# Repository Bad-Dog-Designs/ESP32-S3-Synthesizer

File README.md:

Project overview:
A custom polyphonic synthesizer built around an ESP32-S3 audio engine communicating with multiple ATmega328p control boards via CAN bus at 500kbps. All boards share synth_params.h as the single source of truth for CAN message definitions.
Hardware boards:

ESP32-S3 — audio engine, MIDI input, I2S DAC output, CAN master
Oscillator boards (ATmega328p, up to 4) — dual oscillator control per board, board ID set by hardware jumpers (both open = board 0)
Commons board (ATmega328p) — filter, envelope, LFO, ring mod, play mode controls
Routing board (ATmega328p) — modulation matrix UI, 12 routes, LED matrix display
Patch board (ATmega328p, pending) — SD card patch storage UI, keypad, VFD/starburst display

ESP32-S3 pin assignments:

I2S: GPIO 4(BCK), 5(WS), 6(DOUT)
CAN TX/RX: GPIO 7/8
MIDI RX: GPIO 16
SD card: GPIO 9(CD), 10(CS), 11(MOSI), 12(SCK), 13(MISO)

Current file set (V11.0):

synth_v11.ino — setup(), loop(), task spawn only
synth_engine.h — all type/struct definitions, extern globals, function prototypes
synth_engine.cpp — globals, voice management, oscillator, filter, LFO, FM, audio task
synth_midi.h/.cpp — MIDI byte processing, noteOn/Off, voice allocation
synth_can.h/.cpp — TWAI setup, systemStartup, processCanMessages, sendCanAck
synth_params.h — shared CAN parameter definitions, all boards

Architecture:

Audio runs on Core 1 via audioTask(), CAN+MIDI runs on Core 0 via loop()
portMUX_TYPE voiceMux protects voice array cross-core access
NUM_VOICES_ACTIVE set dynamically from detected oscillator boards at startup (2 per board)
TWAI rx_queue_len=64 to handle full parameter dumps

Voice model:

Up to 8 voices (MAX_VOICES), typically 6 active (3 oscillator boards)
Even voices (0,2,4,6) are FM/sync masters per board pair
Odd voices (1,3,5,7) are FM/sync slaves — can sync to or be FM-modulated by their partner
FM: OSC_A (even) modulates OSC_B (odd) phase. fmEnabled, fmDepth on even voice. fmRatio on odd voice
Hard sync: per-board-pair, not global. syncEnabled only valid on odd voices
Solo: toggle per voice, restricts noteOn to soloed voices only
Clone: copies all timbre params including fmEnabled, fmDepth, fmRatio to all other voices. cloneActive global drives all clone LEDs on all boards simultaneously. Second press clears LEDs, cloned params remain

Signal chain per voice:
S+H → phaseInc | FM phase offset | Oscillator → Wavefold → SVF Filter → × envLevel × level × velocity
Waveforms: SAW, SINE, TRI, PULSE, CHAOS (logistic map), NOISE
Modifiers:

FOLD: post-oscillator waveshaper. foldEnabled, foldAmount (0-1), foldBias (-1 to +1)
S+H: independent pitch randomiser clock. shEnabled, shRate (0.5-40Hz), shRange (1-48 semitones)
FM: fmEnabled, fmDepth (0-1), fmRatio (0.5-8.0)

Play modes: POLY, DUO (half voices per note), UNISON (all voices per note)
Gain scaling by mode: UNISON=1.8f, DUO=2.0f, POLY=4.0f (tuned by ear)
SVF Filter: Low/Band/High pass. cutoffHz, resonance, envAmount (envelope→cutoff), keyTracking. Coefficients updated on each filter parameter change and at noteOn.
Envelope: ADSR. Times stored as float seconds. Coefficients (attackCoeff etc.) computed by updateEnvelopeRates() — must be called at startup and on any time change.
LFOs: 2× LFOs. 4 waveforms (SINE/TRI/CHAOS/S&H). Rate, delay, retrigger. No depth — depth is per-route. RETRIGGER is toggle: each CAN message flips state.
Ring modulator: 4 voice pair options. level, modMute.
Modulation routing (V11 — implementation pending):

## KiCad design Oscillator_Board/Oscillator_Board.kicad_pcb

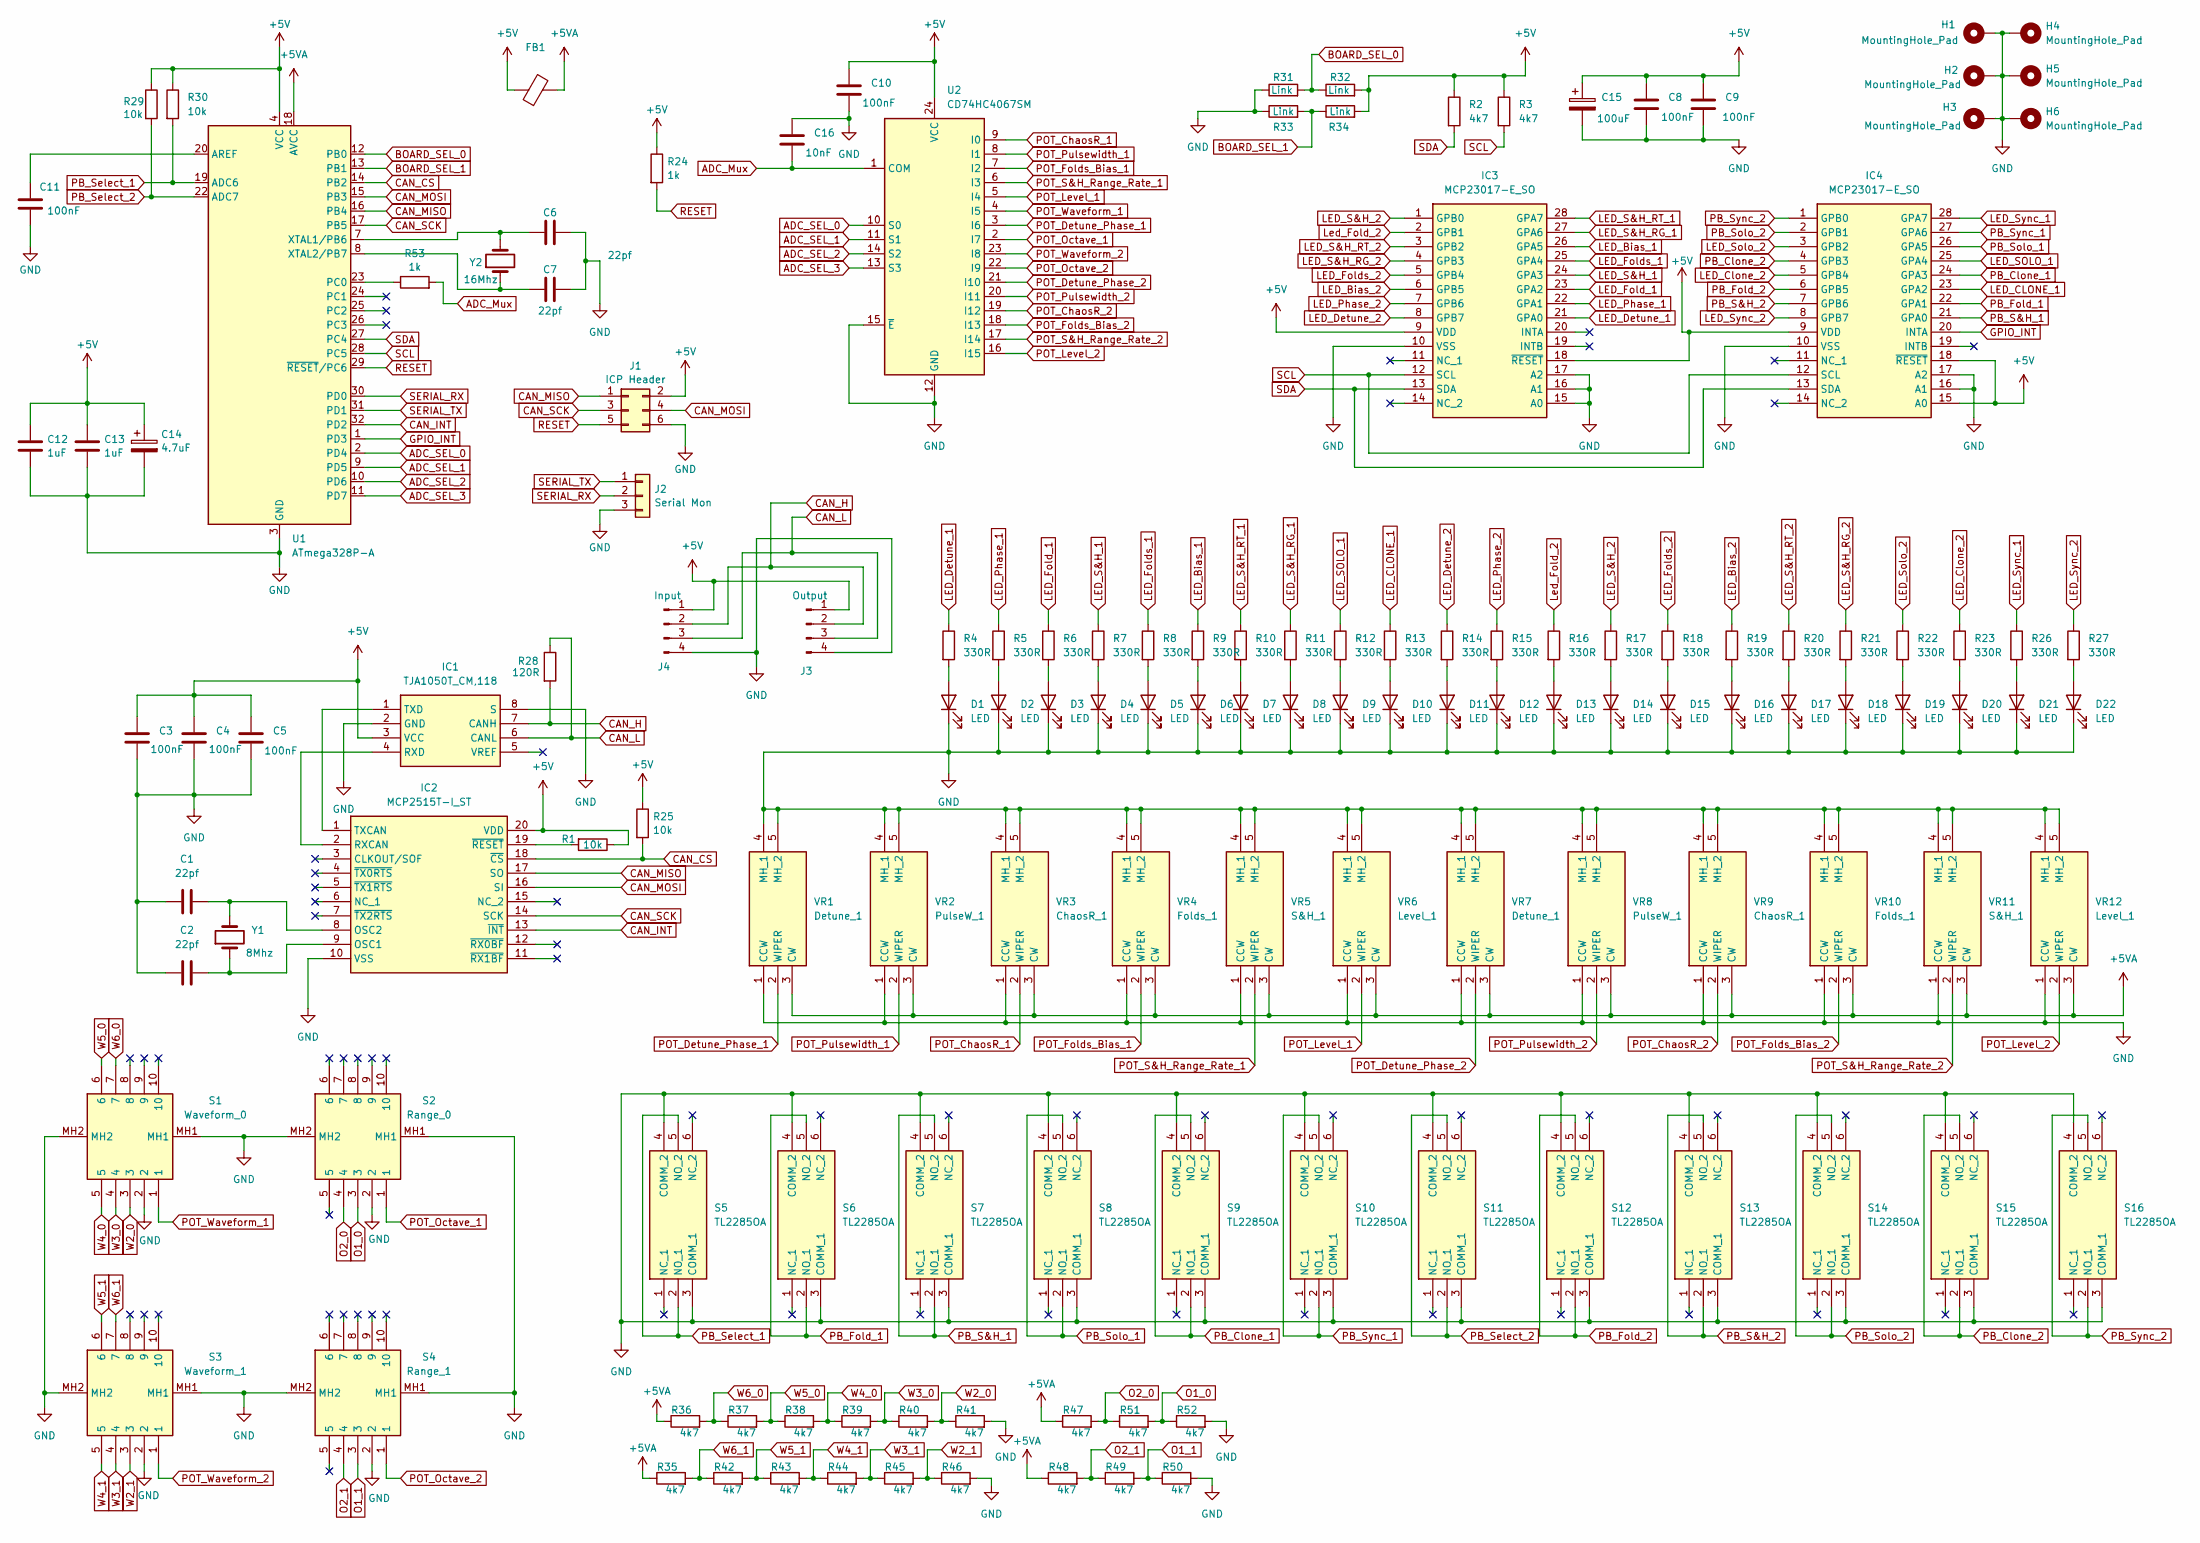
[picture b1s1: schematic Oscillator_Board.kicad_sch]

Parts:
C1, C2, C6, C7: 22pf; C_0805_2012Metric_Pad1.18x1.45mm_HandSolder
C3, C4, C5, C8, C9, C10, C11: 100nF; C_0805_2012Metric_Pad1.18x1.45mm_HandSolder
C12, C13: 1uF; C_0805_2012Metric_Pad1.18x1.45mm_HandSolder
C14: 4.7uF; CP_Radial_D4.0mm_P2.00mm
C15: 100uF; CP_Radial_D4.0mm_P2.00mm
C16: 10nF; C_0805_2012Metric_Pad1.18x1.45mm_HandSolder
D1, D2, D3, D4, D5, D6, D7, D8, D9, D10, D11, D12, D13, D14, D15, D16, D17, D18, D19, D20, D21, D22: LED; LED_D3.0mm_FlatTop
FB1: 10R; R_0805_2012Metric_Pad1.20x1.40mm_HandSolder
H1, H2, H3, H4, H5, H6: MountingHole_Pad; MountingHole_3.2mm_M3_DIN965_Pad
IC1: TJA1050T_CM,118; SOIC127P600X175-8N; Mouser Part Number 771-TJA1050T/CM118
IC2: MCP2515T-I_ST; SOP65P640X120-20N; Mouser Part Number 579-MCP2515T-I/ST
IC3, IC4: MCP23017-E_SO; SOIC127P1030X265-28N; Mouser Part Number 579-MCP23017-E/SO
J1: ICP Header; PinSocket_2x03_P2.54mm_Vertical
J2: Serial Mon; PinSocket_1x03_P2.54mm_Vertical
J3: Output; JST_EH_S4B-EH_1x04_P2.50mm_Horizontal
J4: Input; JST_EH_S4B-EH_1x04_P2.50mm_Horizontal
R1, R25, R29, R30: 10k; R_0603_1608Metric_Pad0.98x0.95mm_HandSolder
R2, R3, R35, R36, R37, R38, R39, R40, R41, R42, R43, R44, R45, R46, R47, R48, R49, R50, R51, R52: 4k7; R_0603_1608Metric_Pad0.98x0.95mm_HandSolder
R4, R5, R6, R7, R8, R9, R10, R11, R12, R13, R14, R15, R16, R17, R18, R19, R20, R21, R22, R23, R26, R27: 330R; R_0603_1608Metric_Pad0.98x0.95mm_HandSolder
R24, R53: 1k; R_0603_1608Metric_Pad0.98x0.95mm_HandSolder
R28: 120R; R_1206_3216Metric_Pad1.30x1.75mm_HandSolder
R31, R32, R33, R34: Link; R_0603_1608Metric_Pad0.98x0.95mm_HandSolder
S1: Waveform_0; SR1712F010820F0AN9N027; Mouser Part Number 105-SR1712F-18NS
S2: Range_0; SR1712F010820F0AN9N027; Mouser Part Number 105-SR1712F-18NS
S3: Waveform_1; SR1712F010820F0AN9N027; Mouser Part Number 105-SR1712F-18NS
S4: Range_1; SR1712F010820F0AN9N027; Mouser Part Number 105-SR1712F-18NS
S5, S6, S7, S8, S9, S10, S11, S12, S13, S14, S15, S16: TL2285OA; Mouser Part Number 612-TL2285OA
U1: ATmega328P-A; TQFP-32_7x7mm_P0.8mm
U2: CD74HC4067SM; SSOP-24_5.3x8.2mm_P0.65mm
VR1, VR7: Detune_1; RK09K1130AAU; Mouser Part Number 688-RK09K1130AAU
VR2, VR8: PulseW_1; RK09K1130AAU; Mouser Part Number 688-RK09K1130AAU
VR3, VR9: ChaosR_1; RK09K1130AAU; Mouser Part Number 688-RK09K1130AAU
VR4, VR10: Folds_1; RK09K1130AAU; Mouser Part Number 688-RK09K1130AAU
VR5, VR11: S&H_1; RK09K1130AAU; Mouser Part Number 688-RK09K1130AAU
VR6, VR12: Level_1; RK09K1130AAU; Mouser Part Number 688-RK09K1130AAU
Y1: 8Mhz; Crystal_HC49-4H_Vertical
Y2: 16Mhz; Crystal_HC49-4H_Vertical

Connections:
+5V: C3.1, C4.1, C5.1, C8.1, C9.1, C10.1, C12.1, C13.1, C14.1, C15.1, FB1.1, IC1.3 (VCC), IC2.20 (VDD), IC3.9 (VDD), IC3.18 (~RESET), IC4.9 (VDD), IC4.15 (A0), IC4.18 (~RESET), J1.2, J3.1, J4.1, R1.1, R2.1, R3.1, R24.1, R25.1, R29.1, R30.1, R32.2, R34.2, U1.4 (VCC), U1.6 (VCC), U2.24 (VCC)
+5VA: FB1.2, R35.1, R36.1, R47.1, R48.1, U1.18 (AVCC), VR1.3 (CW), VR2.3 (CW), VR3.3 (CW), VR4.3 (CW), VR5.3 (CW), VR6.3 (CW), VR7.3 (CW), VR8.3 (CW), VR9.3 (CW), VR10.3 (CW), VR11.3 (CW), VR12.3 (CW)
ADC_Mux: C16.2, R53.2, U2.1 (COM)
ADC_SEL_0: U1.2 (PD4), U2.10 (S0)
ADC_SEL_1: U1.9 (PD5), U2.11 (S1)
ADC_SEL_2: U1.10 (PD6), U2.14 (S2)
ADC_SEL_3: U1.11 (PD7), U2.13 (S3)
BOARD_SEL_0: R31.2, R32.1, U1.12 (PB0)
BOARD_SEL_1: R33.2, R34.1, U1.13 (PB1)
CAN_CS: IC2.18 (~CS), R25.2, U1.14 (PB2)
CAN_H: IC1.7 (CANH), J3.2, J4.2, R28.2
CAN_INT: IC2.13 (~INT), U1.32 (PD2)
CAN_L: IC1.6 (CANL), J3.3, J4.3, R28.1
CAN_MISO: IC2.17 (SO), J1.1, U1.16 (PB4)
CAN_MOSI: IC2.16 (SI), J1.4, U1.15 (PB3)
CAN_SCK: IC2.14 (SCK), J1.3, U1.17 (PB5)
GND: C1.1, C2.1, C3.2, C4.2, C5.2, C6.2, C7.2, C8.2, C9.2, C10.2, C11.2, C12.2, C13.2, C14.2, C15.2, C16.1, D1.1 (K), D2.1 (K), D3.1 (K), D4.1 (K), D5.1 (K), D6.1 (K), D7.1 (K), D8.1 (K), D9.1 (K), D10.1 (K), D11.1 (K), D12.1 (K), D13.1 (K), D14.1 (K), D15.1 (K), D16.1 (K), D17.1 (K), D18.1 (K), D19.1 (K), D20.1 (K), D21.1 (K), D22.1 (K), H1.1, H2.1, H3.1, H4.1, H5.1, H6.1, IC1.2 (GND), IC1.8 (S), IC2.10 (VSS), IC3.10 (VSS), IC3.15 (A0), IC3.16 (A1), IC3.17 (A2), IC4.10 (VSS), IC4.16 (A1), IC4.17 (A2), J1.6, J2.3, J3.4, J4.4, R31.1, R33.1, R41.2, R46.2, R50.2, R52.2, S1.2, S1.MH1, S1.MH2, S2.2, S2.MH1, S2.MH2, S3.2, S3.MH1, S3.MH2, S4.2, S4.MH1, S4.MH2, S5.3 (COMM_1), S5.4 (COMM_2), S6.3 (COMM_1), S6.4 (COMM_2), S7.3 (COMM_1), S7.4 (COMM_2), S8.3 (COMM_1), S8.4 (COMM_2), S9.3 (COMM_1), S9.4 (COMM_2), S10.3 (COMM_1), S10.4 (COMM_2), S11.3 (COMM_1), S11.4 (COMM_2), S12.3 (COMM_1), S12.4 (COMM_2), S13.3 (COMM_1), S13.4 (COMM_2), S14.3 (COMM_1), S14.4 (COMM_2), S15.3 (COMM_1), S15.4 (COMM_2), S16.3 (COMM_1), S16.4 (COMM_2), U1.3 (GND), U1.5 (GND), U1.21 (GND), U2.12 (GND), U2.15 (~E), VR1.1 (CCW), VR1.4 (MH_1), VR1.5 (MH_2), VR2.1 (CCW), VR2.4 (MH_1), VR2.5 (MH_2), VR3.1 (CCW), VR3.4 (MH_1), VR3.5 (MH_2), VR4.1 (CCW), VR4.4 (MH_1), VR4.5 (MH_2), VR5.1 (CCW), VR5.4 (MH_1), VR5.5 (MH_2), VR6.1 (CCW), VR6.4 (MH_1), VR6.5 (MH_2), VR7.1 (CCW), VR7.4 (MH_1), VR7.5 (MH_2), VR8.1 (CCW), VR8.4 (MH_1), VR8.5 (MH_2), VR9.1 (CCW), VR9.4 (MH_1), VR9.5 (MH_2), VR10.1 (CCW), VR10.4 (MH_1), VR10.5 (MH_2), VR11.1 (CCW), VR11.4 (MH_1), VR11.5 (MH_2), VR12.1 (CCW), VR12.4 (MH_1), VR12.5 (MH_2)
GPIO_INT: IC4.20 (INTA), U1.1 (PD3)
LED_Bias_1: IC3.26 (GPA5), R9.1
LED_Bias_2: IC3.6 (GPB5), R19.1
LED_CLONE_1: IC4.23 (GPA2), R13.1
LED_Clone_2: IC4.5 (GPB4), R23.1
LED_Detune_1: IC3.21 (GPA0), R4.1
LED_Detune_2: IC3.8 (GPB7), R14.1
LED_Fold_1: IC3.23 (GPA2), R6.1
LED_Folds_1: IC3.25 (GPA4), R8.1
LED_Folds_2: IC3.5 (GPB4), R18.1
LED_Phase_1: IC3.22 (GPA1), R5.1
LED_Phase_2: IC3.7 (GPB6), R15.1
LED_S&H_1: IC3.24 (GPA3), R7.1
LED_S&H_2: IC3.1 (GPB0), R17.1
LED_S&H_RG_1: IC3.27 (GPA6), R11.1
LED_S&H_RG_2: IC3.4 (GPB3), R21.1
LED_S&H_RT_1: IC3.28 (GPA7), R10.1
LED_S&H_RT_2: IC3.3 (GPB2), R20.1
LED_SOLO_1: IC4.25 (GPA4), R12.1
LED_Solo_2: IC4.3 (GPB2), R22.1
LED_Sync_1: IC4.28 (GPA7), R26.1
LED_Sync_2: IC4.8 (GPB7), R27.1
Led_Fold_2: IC3.2 (GPB1), R16.1
unnamed: D1.2 (A), R4.2
unnamed: D2.2 (A), R5.2
unnamed: D3.2 (A), R6.2
unnamed: D4.2 (A), R7.2
unnamed: D5.2 (A), R8.2
unnamed: D6.2 (A), R9.2
unnamed: D7.2 (A), R10.2
unnamed: D8.2 (A), R11.2
unnamed: D9.2 (A), R12.2
unnamed: D10.2 (A), R13.2
unnamed: D11.2 (A), R14.2
unnamed: D12.2 (A), R15.2
unnamed: D13.2 (A), R16.2
unnamed: D14.2 (A), R17.2
unnamed: D15.2 (A), R18.2
unnamed: D16.2 (A), R19.2
unnamed: D17.2 (A), R20.2
unnamed: D18.2 (A), R21.2
unnamed: D19.2 (A), R22.2
unnamed: D20.2 (A), R23.2
unnamed: D21.2 (A), R26.2
unnamed: D22.2 (A), R27.2
unnamed: IC1.4 (RXD), IC2.2 (RXCAN)
unnamed: IC1.1 (TXD), IC2.1 (TXCAN)
unnamed: C2.2, IC2.9 (OSC1), Y1.1
unnamed: C1.2, IC2.8 (OSC2), Y1.2
unnamed: IC2.19 (~RESET), R1.2
unnamed: C11.1, U1.20 (AREF)
unnamed: R53.1, U1.23 (PC0)
unnamed: C6.1, U1.7 (XTAL1/PB6), Y2.2
unnamed: C7.1, U1.8 (XTAL2/PB7), Y2.1
O1_0: R51.2, R52.1, S2.3
O1_1: R49.2, R50.1, S4.3
O2_0: R47.2, R51.1, S2.4
O2_1: R48.2, R49.1, S4.4
PB_Clone_1: IC4.24 (GPA3), S9.2 (NO_1), S9.5 (NO_2)
PB_Clone_2: IC4.4 (GPB3), S15.2 (NO_1), S15.5 (NO_2)
PB_Fold_1: IC4.22 (GPA1), S6.2 (NO_1), S6.5 (NO_2)
PB_Fold_2: IC4.6 (GPB5), S12.2 (NO_1), S12.5 (NO_2)
PB_S&H_1: IC4.21 (GPA0), S7.2 (NO_1), S7.5 (NO_2)
PB_S&H_2: IC4.7 (GPB6), S13.2 (NO_1), S13.5 (NO_2)
PB_Select_1: R30.2, S5.2 (NO_1), S5.5 (NO_2), U1.19 (ADC6)
PB_Select_2: R29.2, S11.2 (NO_1), S11.5 (NO_2), U1.22 (ADC7)
PB_Solo_1: IC4.26 (GPA5), S8.2 (NO_1), S8.5 (NO_2)
PB_Solo_2: IC4.2 (GPB1), S14.2 (NO_1), S14.5 (NO_2)
PB_Sync_1: IC4.27 (GPA6), S10.2 (NO_1), S10.5 (NO_2)
PB_Sync_2: IC4.1 (GPB0), S16.2 (NO_1), S16.5 (NO_2)
POT_ChaosR_1: U2.9 (I0), VR3.2 (WIPER)
POT_ChaosR_2: U2.19 (I12), VR9.2 (WIPER)
POT_Detune_Phase_1: U2.3 (I6), VR1.2 (WIPER)
POT_Detune_Phase_2: U2.21 (I10), VR7.2 (WIPER)
POT_Folds_Bias_1: U2.7 (I2), VR4.2 (WIPER)
POT_Folds_Bias_2: U2.18 (I13), VR10.2 (WIPER)
POT_Level_1: U2.5 (I4), VR6.2 (WIPER)
POT_Level_2: U2.16 (I15), VR12.2 (WIPER)
POT_Octave_1: S2.1, U2.2 (I7)
POT_Octave_2: S4.1, U2.22 (I9)
POT_Pulsewidth_1: U2.8 (I1), VR2.2 (WIPER)
POT_Pulsewidth_2: U2.20 (I11), VR8.2 (WIPER)
POT_S&H_Range_Rate_1: U2.6 (I3), VR5.2 (WIPER)
POT_S&H_Range_Rate_2: U2.17 (I14), VR11.2 (WIPER)
POT_Waveform_1: S1.1, U2.4 (I5)
POT_Waveform_2: S3.1, U2.23 (I8)
RESET: J1.5, R24.2, U1.29 (~RESET/PC6)
SCL: IC3.12 (SCL), IC4.12 (SCL), R3.2, U1.28 (PC5)
SDA: IC3.13 (SDA), IC4.13 (SDA), R2.2, U1.27 (PC4)
SERIAL_RX: J2.2, U1.30 (PD0)
SERIAL_TX: J2.1, U1.31 (PD1)
W2_0: R40.2, R41.1, S1.3
W2_1: R45.2, R46.1, S3.3
W3_0: R39.2, R40.1, S1.4
W3_1: R44.2, R45.1, S3.4
W4_0: R38.2, R39.1, S1.5
W4_1: R43.2, R44.1, S3.5
W5_0: R37.2, R38.1, S1.6
W5_1: R42.2, R43.1, S3.6
W6_0: R36.2, R37.1, S1.7
W6_1: R35.2, R42.1, S3.7

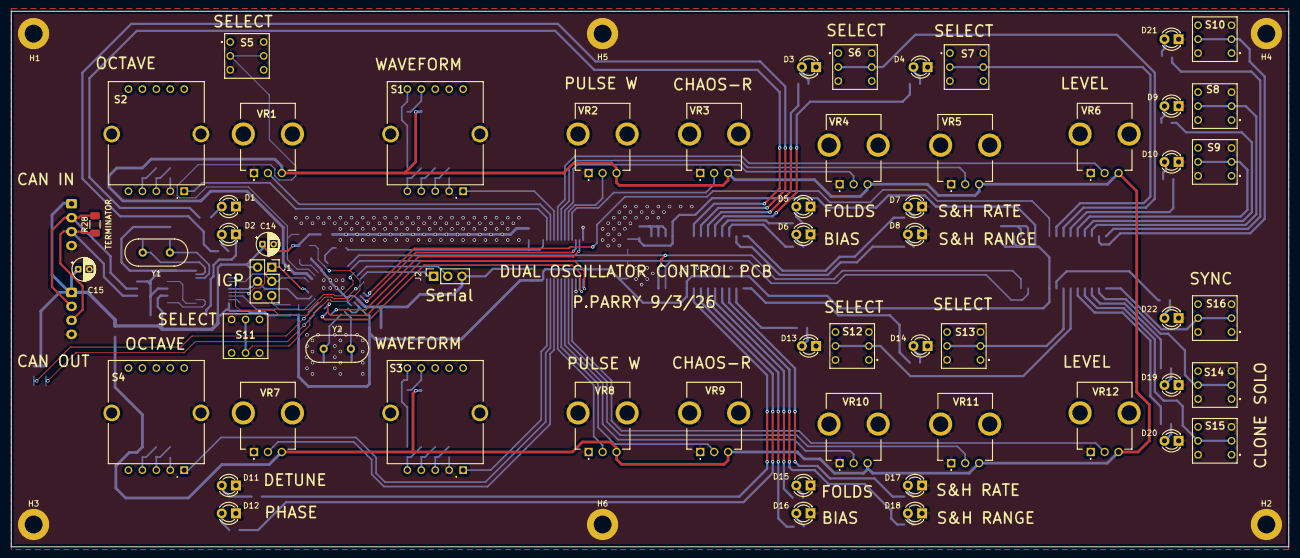
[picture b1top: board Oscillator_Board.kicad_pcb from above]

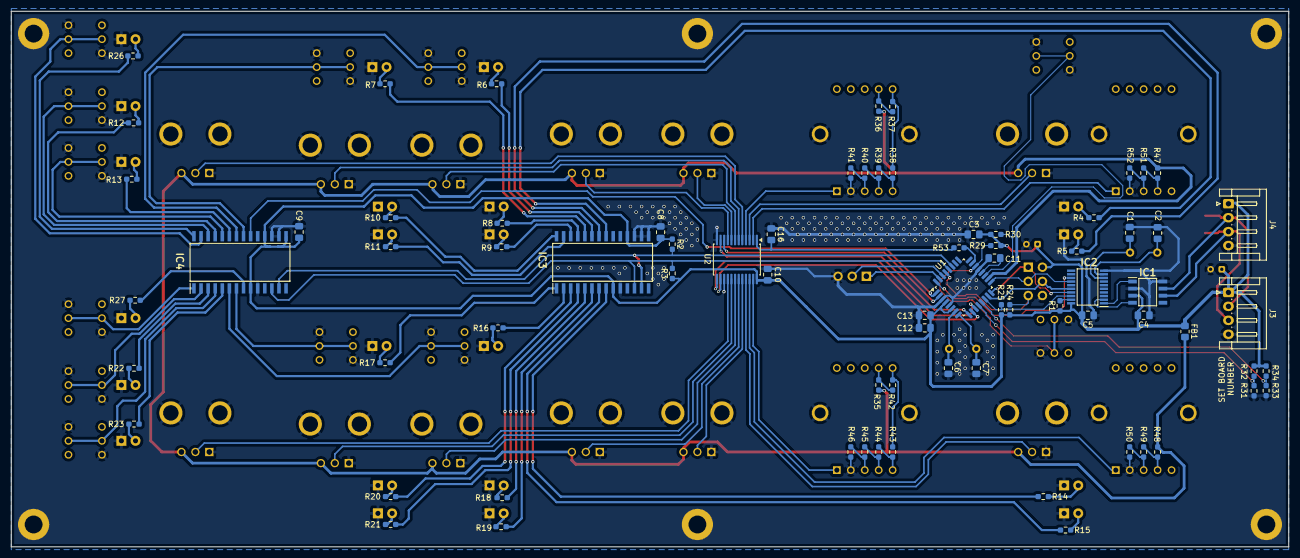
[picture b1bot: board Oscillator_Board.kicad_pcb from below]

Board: 2 copper layers, 229.0 x 96.0 mm, 138 parts (75 on the bottom side), 118 nets.

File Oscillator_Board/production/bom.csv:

Designator,Footprint,Quantity,Value,LCSC Part #
"C1, C2, C6, C7",0805,4,22pf,
"C10, C11, C3, C4, C5, C8, C9",0805,7,100nF,
"C12, C13",0805,2,1uF,
C14,CP_Radial_D4.0mm_P2.00mm,1,4.7uF,
C15,CP_Radial_D4.0mm_P2.00mm,1,100uF,
C16,0805,1,10nF,
"D1, D10, D11, D12, D13, D14, D15, D16, D17, D18, D19, D2, D20, D21, D22, D3, D4, D5, D6, D7, D8, D9",LED_D3.0mm_FlatTop,22,LED,
FB1,0805,1,10R,
IC1,SOIC127P600X175-8N,1,"TJA1050T_CM,118",
IC2,SOP65P640X120-20N,1,MCP2515T-I_ST,
"IC3, IC4",SOIC127P1030X265-28N,2,MCP23017-E_SO,
J1,PinSocket_2x03_P2.54mm_Vertical,1,ICP Header,
J2,PinSocket_1x03_P2.54mm_Vertical,1,Serial Mon,
J3,JST_EH_S4B-EH_1x04_P2.50mm_Horizontal,1,Output,
J4,JST_EH_S4B-EH_1x04_P2.50mm_Horizontal,1,Input,
"R1, R25, R29, R30",0603,4,10k,
"R10, R11, R12, R13, R14, R15, R16, R17, R18, R19, R20, R21, R22, R23, R26, R27, R4, R5, R6, R7, R8, R9",0603,22,330R,
"R2, R3, R35, R36, R37, R38, R39, R40, R41, R42, R43, R44, R45, R46, R47, R48, R49, R50, R51, R52",0603,20,4k7,
"R24, R53",0603,2,1k,
R28,1206,1,120R,
"R31, R32, R33, R34",0603,4,Link,
S1,SR1712F010820F0AN9N027,1,Waveform_0,
"S10, S11, S12, S13, S14, S15, S16, S5, S6, S7, S8, S9",TL2285OA,12,TL2285OA,
S2,SR1712F010820F0AN9N027,1,Range_0,
S3,SR1712F010820F0AN9N027,1,Waveform_1,
S4,SR1712F010820F0AN9N027,1,Range_1,
U1,TQFP-32_7x7mm_P0.8mm,1,ATmega328P-A,
U2,SSOP-24_5.3x8.2mm_P0.65mm,1,CD74HC4067SM,
"VR1, VR7",RK09K1130AAU,2,Detune_1,
"VR10, VR4",RK09K1130AAU,2,Folds_1,
"VR11, VR5",RK09K1130AAU,2,S&H_1,
"VR12, VR6",RK09K1130AAU,2,Level_1,
"VR2, VR8",RK09K1130AAU,2,PulseW_1,
"VR3, VR9",RK09K1130AAU,2,ChaosR_1,
Y1,Crystal_HC49-4H_Vertical,1,8Mhz,
Y2,Crystal_HC49-4H_Vertical,1,16Mhz,

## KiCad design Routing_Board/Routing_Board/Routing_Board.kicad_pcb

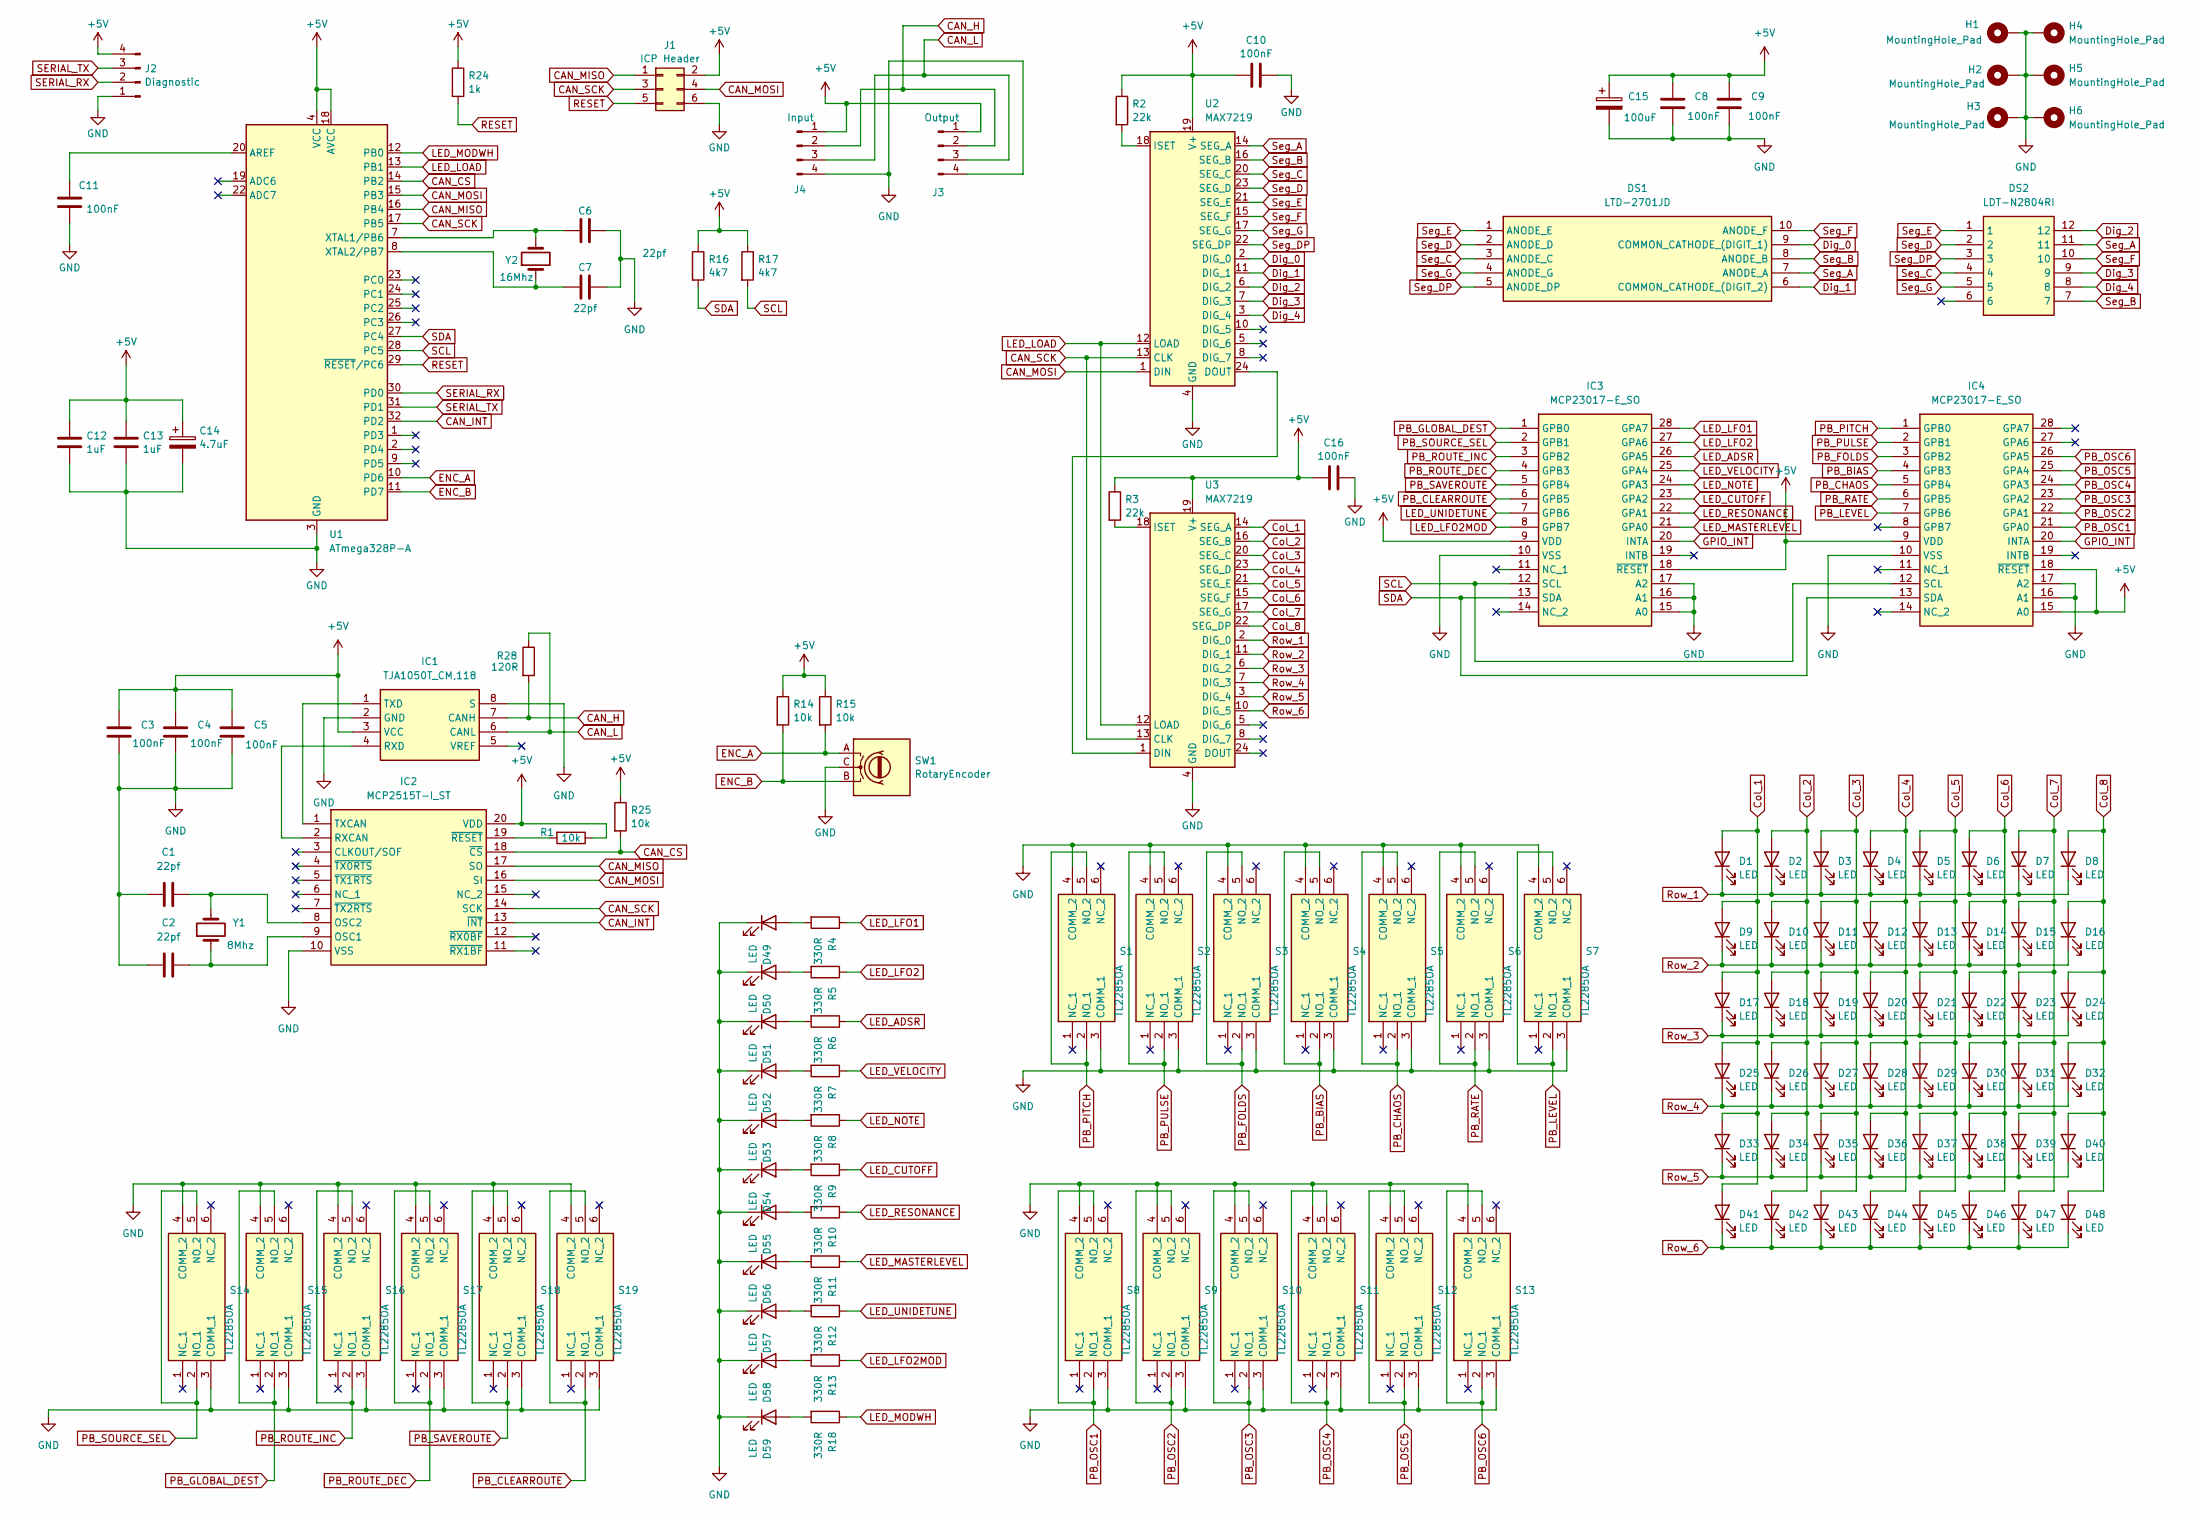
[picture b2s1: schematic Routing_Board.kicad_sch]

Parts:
C1, C2, C6, C7: 22pf; C_0805_2012Metric_Pad1.18x1.45mm_HandSolder
C3, C4, C5, C8, C9, C10, C11, C16: 100nF; C_0805_2012Metric_Pad1.18x1.45mm_HandSolder
C12, C13: 1uF; C_0805_2012Metric_Pad1.18x1.45mm_HandSolder
C14: 4.7uF; CP_Radial_D4.0mm_P2.00mm
C15: 100uF; CP_Radial_D4.0mm_P2.00mm
D1, D2, D3, D4, D5, D6, D7, D8, D9, D10, D11, D12, D13, D14, D15, D16, D17, D18, D19, D20, D21, D22, D23, D24, D25, D26, D27, D28, D29, D30, D31, D32, D33, D34, D35, D36, D37, D38, D39, D40, D41, D42, D43, D44, D45, D46, D47, D48, D49, D50, D51, D52, D53, D54, D55, D56, D57, D58, D59: LED; LED_D3.0mm_FlatTop
DS1: LTD-2701JD; DIPS762W50P254L1502H635Q10N; Mouser Part Number 859-LTD-2701JD
DS2: LDT-N2804RI; DIPS762W45P254L2253H610Q12N; Mouser Part Number 696-LDT-N2804RI
H1, H2, H3, H4, H5, H6: MountingHole_Pad; MountingHole_3.2mm_M3_DIN965_Pad
IC1: TJA1050T_CM,118; SOIC127P600X175-8N; Mouser Part Number 771-TJA1050T/CM118
IC2: MCP2515T-I_ST; SOP65P640X120-20N; Mouser Part Number 579-MCP2515T-I/ST
IC3, IC4: MCP23017-E_SO; SOIC127P1030X265-28N; Mouser Part Number 579-MCP23017-E/SO
J1: ICP Header; PinSocket_2x03_P2.54mm_Vertical
J2: Diagnostic; PinHeader_1x04_P2.54mm_Vertical
J3: Output; JST_EH_S4B-EH_1x04_P2.50mm_Horizontal
J4: Input; JST_EH_S4B-EH_1x04_P2.50mm_Horizontal
R1, R25: 10k; R_0603_1608Metric_Pad0.98x0.95mm_HandSolder
R2, R3: 22k; R_0805_2012Metric_Pad1.20x1.40mm_HandSolder
R4, R5, R6, R7, R8, R9, R10, R11, R12, R13, R18: 330R; R_0603_1608Metric_Pad0.98x0.95mm_HandSolder
R14, R15: 10k; R_0805_2012Metric_Pad1.20x1.40mm_HandSolder
R16, R17: 4k7; R_0805_2012Metric_Pad1.20x1.40mm_HandSolder
R24: 1k; R_0603_1608Metric_Pad0.98x0.95mm_HandSolder
R28: 120R; R_1206_3216Metric_Pad1.30x1.75mm_HandSolder
S1, S2, S3, S4, S5, S6, S7, S8, S9, S10, S11, S12, S13, S14, S15, S16, S17, S18, S19: TL2285OA; Mouser Part Number 612-TL2285OA
SW1: RotaryEncoder; RotaryEncoder_Alps_EC12E_Vertical_H20mm
U1: ATmega328P-A; TQFP-32_7x7mm_P0.8mm
U2, U3: MAX7219; SOIC-24W_7.5x15.4mm_P1.27mm
Y1: 8Mhz; Crystal_HC49-4H_Vertical
Y2: 16Mhz; Crystal_HC49-4H_Vertical

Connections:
+5V: C3.1, C4.1, C5.1, C8.1, C9.1, C10.1, C12.1, C13.1, C14.1, C15.1, C16.1, IC1.3 (VCC), IC2.20 (VDD), IC3.9 (VDD), IC3.18 (~RESET), IC4.9 (VDD), IC4.15 (A0), IC4.18 (~RESET), J1.2, J2.4, J3.1, J4.1, R1.1, R2.1, R3.1, R14.1, R15.1, R16.1, R17.1, R24.1, R25.1, U1.4 (VCC), U1.6 (VCC), U1.18 (AVCC), U2.19 (V+), U3.19 (V+)
CAN_CS: IC2.18 (~CS), R25.2, U1.14 (PB2)
CAN_H: IC1.7 (CANH), J3.2, J4.2, R28.2
CAN_INT: IC2.13 (~INT), U1.32 (PD2)
CAN_L: IC1.6 (CANL), J3.3, J4.3, R28.1
CAN_MISO: IC2.17 (SO), J1.1, U1.16 (PB4)
CAN_MOSI: IC2.16 (SI), J1.4, U1.15 (PB3), U2.1 (DIN)
CAN_SCK: IC2.14 (SCK), J1.3, U1.17 (PB5), U2.13 (CLK), U3.13 (CLK)
Col_1: D1.2 (A), D9.2 (A), D17.2 (A), D25.2 (A), D33.2 (A), D41.2 (A), U3.14 (SEG_A)
Col_2: D2.2 (A), D10.2 (A), D18.2 (A), D26.2 (A), D34.2 (A), D42.2 (A), U3.16 (SEG_B)
Col_3: D3.2 (A), D11.2 (A), D19.2 (A), D27.2 (A), D35.2 (A), D43.2 (A), U3.20 (SEG_C)
Col_4: D4.2 (A), D12.2 (A), D20.2 (A), D28.2 (A), D36.2 (A), D44.2 (A), U3.23 (SEG_D)
Col_5: D5.2 (A), D13.2 (A), D21.2 (A), D29.2 (A), D37.2 (A), D45.2 (A), U3.21 (SEG_E)
Col_6: D6.2 (A), D14.2 (A), D22.2 (A), D30.2 (A), D38.2 (A), D46.2 (A), U3.15 (SEG_F)
Col_7: D7.2 (A), D15.2 (A), D23.2 (A), D31.2 (A), D39.2 (A), D47.2 (A), U3.17 (SEG_G)
Col_8: D8.2 (A), D16.2 (A), D24.2 (A), D32.2 (A), D40.2 (A), D48.2 (A), U3.22 (SEG_DP)
Dig_0: DS1.9 (COMMON_CATHODE_(DIGIT_1)), U2.2 (DIG_0)
Dig_1: DS1.6 (COMMON_CATHODE_(DIGIT_2)), U2.11 (DIG_1)
Dig_2: DS2.12, U2.6 (DIG_2)
Dig_3: DS2.9, U2.7 (DIG_3)
Dig_4: DS2.8, U2.3 (DIG_4)
ENC_A: R15.2, SW1.A, U1.10 (PD6)
ENC_B: R14.2, SW1.B, U1.11 (PD7)
GND: C1.1, C2.1, C3.2, C4.2, C5.2, C6.2, C7.2, C8.2, C9.2, C10.2, C11.2, C12.2, C13.2, C14.2, C15.2, C16.2, D49.1 (K), D50.1 (K), D51.1 (K), D52.1 (K), D53.1 (K), D54.1 (K), D55.1 (K), D56.1 (K), D57.1 (K), D58.1 (K), D59.1 (K), H1.1, H2.1, H3.1, H4.1, H5.1, H6.1, IC1.2 (GND), IC1.8 (S), IC2.10 (VSS), IC3.10 (VSS), IC3.15 (A0), IC3.16 (A1), IC3.17 (A2), IC4.10 (VSS), IC4.16 (A1), IC4.17 (A2), J1.6, J2.1, J3.4, J4.4, S1.3 (COMM_1), S1.4 (COMM_2), S2.3 (COMM_1), S2.4 (COMM_2), S3.3 (COMM_1), S3.4 (COMM_2), S4.3 (COMM_1), S4.4 (COMM_2), S5.3 (COMM_1), S5.4 (COMM_2), S6.3 (COMM_1), S6.4 (COMM_2), S7.3 (COMM_1), S7.4 (COMM_2), S8.3 (COMM_1), S8.4 (COMM_2), S9.3 (COMM_1), S9.4 (COMM_2), S10.3 (COMM_1), S10.4 (COMM_2), S11.3 (COMM_1), S11.4 (COMM_2), S12.3 (COMM_1), S12.4 (COMM_2), S13.3 (COMM_1), S13.4 (COMM_2), S14.3 (COMM_1), S14.4 (COMM_2), S15.3 (COMM_1), S15.4 (COMM_2), S16.3 (COMM_1), S16.4 (COMM_2), S17.3 (COMM_1), S17.4 (COMM_2), S18.3 (COMM_1), S18.4 (COMM_2), S19.3 (COMM_1), S19.4 (COMM_2), SW1.C, U1.3 (GND), U1.5 (GND), U1.21 (GND), U2.4 (GND), U2.9 (GND), U3.4 (GND), U3.9 (GND)
GPIO_INT: IC3.20 (INTA), IC4.20 (INTA)
LED_ADSR: IC3.26 (GPA5), R6.1
LED_CUTOFF: IC3.23 (GPA2), R9.1
LED_LFO1: IC3.28 (GPA7), R4.1
LED_LFO2: IC3.27 (GPA6), R5.1
LED_LFO2MOD: IC3.8 (GPB7), R13.1
LED_LOAD: U1.13 (PB1), U2.12 (LOAD), U3.12 (LOAD)
LED_MASTERLEVEL: IC3.21 (GPA0), R11.1
LED_MODWH: R18.1, U1.12 (PB0)
LED_NOTE: IC3.24 (GPA3), R8.1
LED_RESONANCE: IC3.22 (GPA1), R10.1
LED_UNIDETUNE: IC3.7 (GPB6), R12.1
LED_VELOCITY: IC3.25 (GPA4), R7.1
unnamed: D49.2 (A), R4.2
unnamed: D50.2 (A), R5.2
unnamed: D51.2 (A), R6.2
unnamed: D52.2 (A), R7.2
unnamed: D53.2 (A), R8.2
unnamed: D54.2 (A), R9.2
unnamed: D55.2 (A), R10.2
unnamed: D56.2 (A), R11.2
unnamed: D57.2 (A), R12.2
unnamed: D58.2 (A), R13.2
unnamed: D59.2 (A), R18.2
unnamed: IC1.4 (RXD), IC2.2 (RXCAN)
unnamed: IC1.1 (TXD), IC2.1 (TXCAN)
unnamed: C2.2, IC2.9 (OSC1), Y1.1
unnamed: C1.2, IC2.8 (OSC2), Y1.2
unnamed: IC2.19 (~RESET), R1.2
unnamed: C11.1, U1.20 (AREF)
unnamed: C6.1, U1.7 (XTAL1/PB6), Y2.2
unnamed: C7.1, U1.8 (XTAL2/PB7), Y2.1
unnamed: U2.24 (DOUT), U3.1 (DIN)
unnamed: R2.2, U2.18 (ISET)
unnamed: R3.2, U3.18 (ISET)
PB_BIAS: IC4.4 (GPB3), S4.2 (NO_1), S4.5 (NO_2)
PB_CHAOS: IC4.5 (GPB4), S5.2 (NO_1), S5.5 (NO_2)
PB_CLEARROUTE: IC3.6 (GPB5), S19.2 (NO_1), S19.5 (NO_2)
PB_FOLDS: IC4.3 (GPB2), S3.2 (NO_1), S3.5 (NO_2)
PB_GLOBAL_DEST: IC3.1 (GPB0), S15.2 (NO_1), S15.5 (NO_2)
PB_LEVEL: IC4.7 (GPB6), S7.2 (NO_1), S7.5 (NO_2)
PB_OSC1: IC4.21 (GPA0), S8.2 (NO_1), S8.5 (NO_2)
PB_OSC2: IC4.22 (GPA1), S9.2 (NO_1), S9.5 (NO_2)
PB_OSC3: IC4.23 (GPA2), S10.2 (NO_1), S10.5 (NO_2)
PB_OSC4: IC4.24 (GPA3), S11.2 (NO_1), S11.5 (NO_2)
PB_OSC5: IC4.25 (GPA4), S12.2 (NO_1), S12.5 (NO_2)
PB_OSC6: IC4.26 (GPA5), S13.2 (NO_1), S13.5 (NO_2)
PB_PITCH: IC4.1 (GPB0), S1.2 (NO_1), S1.5 (NO_2)
PB_PULSE: IC4.2 (GPB1), S2.2 (NO_1), S2.5 (NO_2)
PB_RATE: IC4.6 (GPB5), S6.2 (NO_1), S6.5 (NO_2)
PB_ROUTE_DEC: IC3.4 (GPB3), S17.2 (NO_1), S17.5 (NO_2)
PB_ROUTE_INC: IC3.3 (GPB2), S16.2 (NO_1), S16.5 (NO_2)
PB_SAVEROUTE: IC3.5 (GPB4), S18.2 (NO_1), S18.5 (NO_2)
PB_SOURCE_SEL: IC3.2 (GPB1), S14.2 (NO_1), S14.5 (NO_2)
RESET: J1.5, R24.2, U1.29 (~RESET/PC6)
Row_1: D1.1 (K), D2.1 (K), D3.1 (K), D4.1 (K), D5.1 (K), D6.1 (K), D7.1 (K), D8.1 (K), U3.2 (DIG_0)
Row_2: D9.1 (K), D10.1 (K), D11.1 (K), D12.1 (K), D13.1 (K), D14.1 (K), D15.1 (K), D16.1 (K), U3.11 (DIG_1)
Row_3: D17.1 (K), D18.1 (K), D19.1 (K), D20.1 (K), D21.1 (K), D22.1 (K), D23.1 (K), D24.1 (K), U3.6 (DIG_2)
Row_4: D25.1 (K), D26.1 (K), D27.1 (K), D28.1 (K), D29.1 (K), D30.1 (K), D31.1 (K), D32.1 (K), U3.7 (DIG_3)
Row_5: D33.1 (K), D34.1 (K), D35.1 (K), D36.1 (K), D37.1 (K), D38.1 (K), D39.1 (K), D40.1 (K), U3.3 (DIG_4)
Row_6: D41.1 (K), D42.1 (K), D43.1 (K), D44.1 (K), D45.1 (K), D46.1 (K), D47.1 (K), D48.1 (K), U3.10 (DIG_5)
SCL: IC3.12 (SCL), IC4.12 (SCL), R17.2, U1.28 (PC5)
SDA: IC3.13 (SDA), IC4.13 (SDA), R16.2, U1.27 (PC4)
SERIAL_RX: J2.2, U1.30 (PD0)
SERIAL_TX: J2.3, U1.31 (PD1)
Seg_A: DS1.7 (ANODE_A), DS2.11, U2.14 (SEG_A)
Seg_B: DS1.8 (ANODE_B), DS2.7, U2.16 (SEG_B)
Seg_C: DS1.3 (ANODE_C), DS2.4, U2.20 (SEG_C)
Seg_D: DS1.2 (ANODE_D), DS2.2, U2.23 (SEG_D)
Seg_DP: DS1.5 (ANODE_DP), DS2.3, U2.22 (SEG_DP)
Seg_E: DS1.1 (ANODE_E), DS2.1, U2.21 (SEG_E)
Seg_F: DS1.10 (ANODE_F), DS2.10, U2.15 (SEG_F)
Seg_G: DS1.4 (ANODE_G), DS2.5, U2.17 (SEG_G)

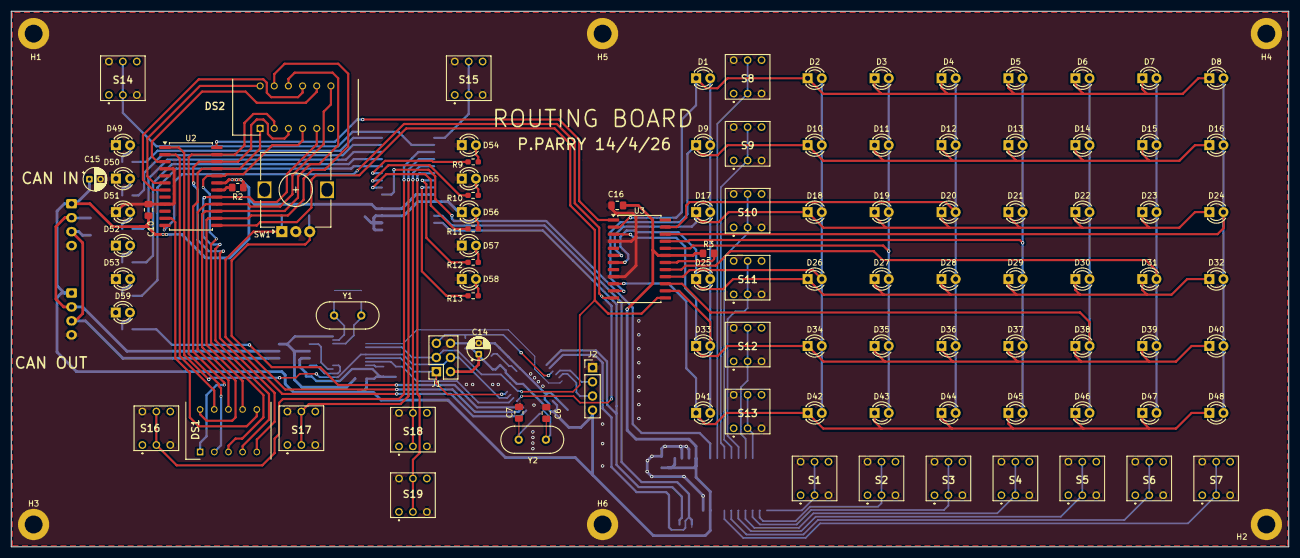
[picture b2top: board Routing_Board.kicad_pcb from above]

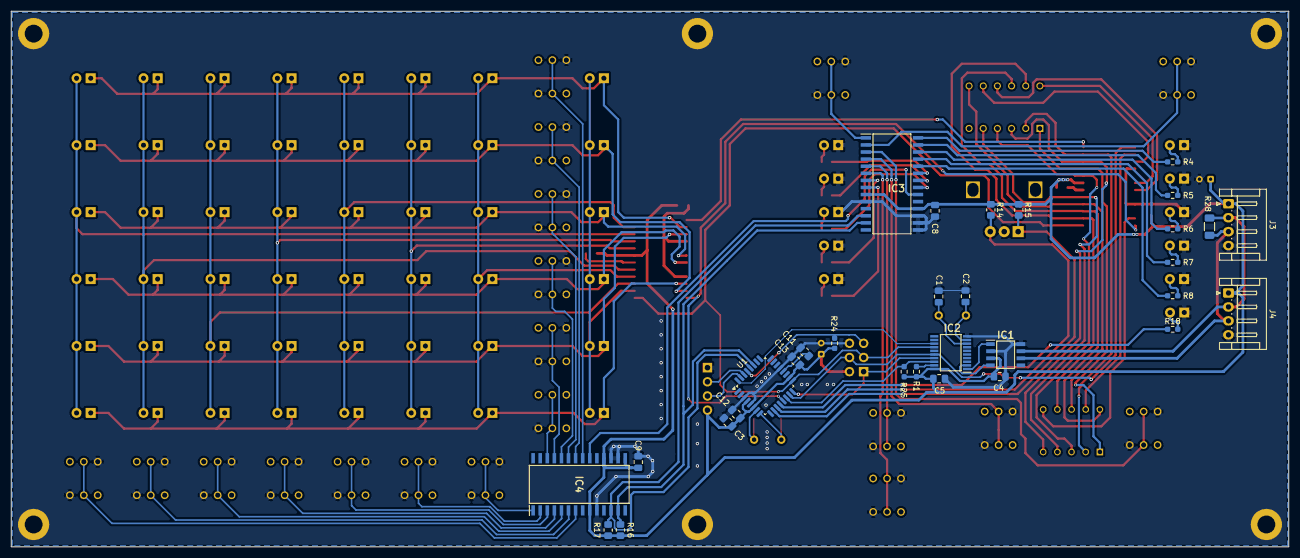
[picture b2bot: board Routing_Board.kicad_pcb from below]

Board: 2 copper layers, 229.0 x 96.0 mm, 137 parts (31 on the bottom side), 97 nets.

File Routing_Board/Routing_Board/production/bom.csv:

Designator,Footprint,Quantity,Value,LCSC Part #
"C1, C2, C6, C7",0805,4,22pf,
"C10, C11, C16, C3, C4, C5, C8, C9",0805,8,100nF,
"C12, C13",0805,2,1uF,
C14,CP_Radial_D4.0mm_P2.00mm,1,4.7uF,
C15,CP_Radial_D4.0mm_P2.00mm,1,100uF,
"D1, D10, D11, D12, D13, D14, D15, D16, D17, D18, D19, D2, D20, D21, D22, D23, D24, D25, D26, D27, D28, D29, D3, D30, D31, D32, D33, D34, D35, D36, D37, D38, D39, D4, D40, D41, D42, D43, D44, D45, D46, D47, D48, D49, D5, D50, D51, D52, D53, D54, D55, D56, D57, D58, D59, D6, D7, D8, D9",LED_D3.0mm_FlatTop,59,LED,
DS1,DIPS762W50P254L1502H635Q10N,1,LTD-2701JD,
DS2,DIPS762W45P254L2253H610Q12N,1,LDT-N2804RI,
IC1,SOIC127P600X175-8N,1,"TJA1050T_CM,118",
IC2,SOP65P640X120-20N,1,MCP2515T-I_ST,
"IC3, IC4",SOIC127P1030X265-28N,2,MCP23017-E_SO,
J1,PinSocket_2x03_P2.54mm_Vertical,1,ICP Header,
J2,PinHeader_1x04_P2.54mm_Vertical,1,Diagnostic,
J3,JST_EH_S4B-EH_1x04_P2.50mm_Horizontal,1,Output,
J4,JST_EH_S4B-EH_1x04_P2.50mm_Horizontal,1,Input,
"R1, R25",0603,2,10k,
"R10, R11, R12, R13, R18, R4, R5, R6, R7, R8, R9",0603,11,330R,
"R14, R15",0805,2,10k,
"R16, R17",0805,2,4k7,
"R2, R3",0805,2,22k,
R24,0603,1,1k,
R28,1206,1,120R,
"S1, S10, S11, S12, S13, S14, S15, S16, S17, S18, S19, S2, S3, S4, S5, S6, S7, S8, S9",TL2285OA,19,TL2285OA,
SW1,RotaryEncoder_Alps_EC12E_Vertical_H20mm,1,RotaryEncoder,
U1,TQFP-32_7x7mm_P0.8mm,1,ATmega328P-A,
"U2, U3",SOIC-24W_7.5x15.4mm_P1.27mm,2,MAX7219,
Y1,Crystal_HC49-4H_Vertical,1,8Mhz,
Y2,Crystal_HC49-4H_Vertical,1,16Mhz,
